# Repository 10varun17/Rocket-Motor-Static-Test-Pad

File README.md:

# Rocket-Motor-Static-Test-Pad
</br>
This project includes the work that I did during my internship at the Space Technology and Aeronautical Rocketry (STAR) Labs, India in 2022. The objective of my task in the internship was to design a Rocket Motor Static Test Pad for testing and acquiring the required data for the performance analysis of the high powered rocket motors. It is not an individual project. My project had two departments: Avionics and Mechanical Design. There were two members in the Mechanical Design Department and one member (that's me!) in the Avionics Department. I have added my internship report to this repo. Please go through the report to understand the work I did during the internship. The report is an individual report, but during the internship, I was told to put ~80% of my work (avionics) and 20% of my teammates' work in the report. It means that I do not have any contributions to the CAD designs that are presented in my report. My work in the project includes the Avionics work only.</br>

<h2>Notes</h2></br>
You need to have the softwares Proteus and Eagle EDA to open the files in the Circuit Design and PCB design sub-directories. However, I have put some images and pdfs to show my circuit and PCB designs.

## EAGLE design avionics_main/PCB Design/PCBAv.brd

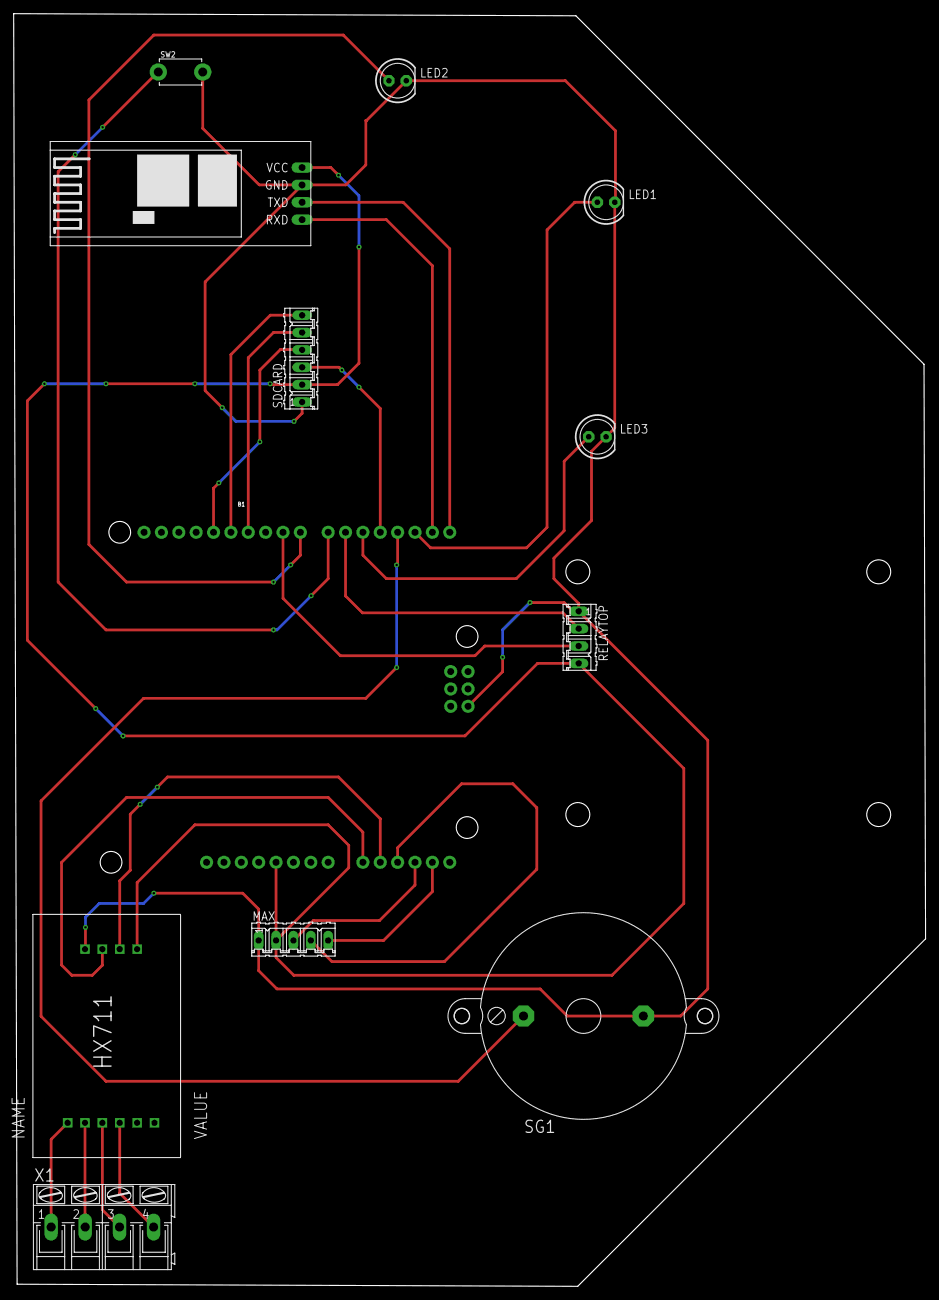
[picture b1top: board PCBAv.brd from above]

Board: 2 copper layers, 133.4 x 186.1 mm, 12 parts (0 on the bottom side), 24 nets.

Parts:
B1: ARDUINO_UNO_R3; ARDUINO_R3
HC05: BLUETOOTH
LED1: Green; LED5MM
LED2: Red; LED5MM
LED3: Yellow; LED5MM
MAX: 05P
RELAYTOP: 04P
SDCARD: 06P
SG1: F/BC35
SW2: TACT_PANA-EVQ
U$1: HX711
X1: AK300/4

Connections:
3.3V: B1.GND@4, HC05.3, LED1.K, LED2.K, LED3.K, MAX.1, RELAYTOP.1, SDCARD.1, SG1.-, SW2.P$2, U$1.GND
unnamed: B1.D1, HC05.1
unnamed: B1.A0, U$1.DT
unnamed: B1.D0, HC05.2
unnamed: B1.D7, SW2.P$1
unnamed: U$1.E+, X1.1
unnamed: U$1.E-, X1.2
unnamed: U$1.A-, X1.3
unnamed: U$1.A+, X1.4
unnamed: B1.A4, MAX.5
unnamed: B1.A2, MAX.4
unnamed: B1.A3, MAX.3
unnamed: B1.D4, SDCARD.3
unnamed: B1.D11, SDCARD.5
unnamed: B1.D13, SDCARD.4
unnamed: B1.D12, SDCARD.6
unnamed: B1.D8, LED2.A
unnamed: B1.D2, LED1.A
unnamed: B1.D5, LED3.A
unnamed: B1.D3, SG1.+
unnamed: B1.D9, RELAYTOP.3
unnamed: B1.D6, RELAYTOP.2
unnamed: B1.A1, U$1.SCK
VCC: B1.5V, HC05.4, MAX.2, RELAYTOP.4, SDCARD.2, U$1.VCC

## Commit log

2024-07-12 Product ready for development :))
2026-01-23 Add LICENSE file

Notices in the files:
parts and their libraries:
SparkFun-Boards: Licensing: Creative Commons ShareAlike 4.0 International - https://creativecommons.org/licenses/by-sa/4.0
